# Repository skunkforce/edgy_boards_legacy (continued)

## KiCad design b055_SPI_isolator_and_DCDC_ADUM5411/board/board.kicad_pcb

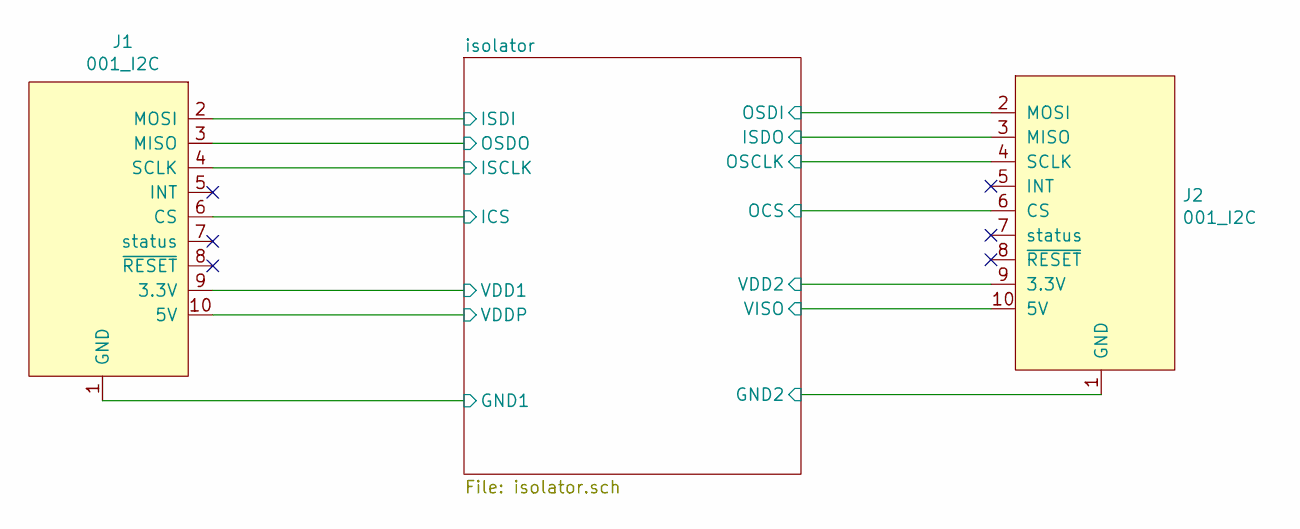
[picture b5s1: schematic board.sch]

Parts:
J1: 001_I2C; on_edge_2x05_device
J2: 001_I2C; on_edge_2x05_host

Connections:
/isolator/GND1: J1.1 (GND); also elsewhere on the board
/isolator/GND2: J2.1 (GND); also elsewhere on the board
/isolator/ICS: J1.6 (CS); also elsewhere on the board
/isolator/ISCLK: J1.4 (SCLK); also elsewhere on the board
/isolator/ISDI: J1.2 (MOSI); also elsewhere on the board
/isolator/ISDO: J2.3 (MISO); also elsewhere on the board
/isolator/OCS: J2.6 (CS); also elsewhere on the board
/isolator/OSCLK: J2.4 (SCLK); also elsewhere on the board
/isolator/OSDI: J2.2 (MOSI); also elsewhere on the board
/isolator/OSDO: J1.3 (MISO); also elsewhere on the board
/isolator/VDD1: J1.9 (3.3V); also elsewhere on the board
/isolator/VDD2: J2.9 (3.3V); also elsewhere on the board
/isolator/VDDP: J1.10 (5V); also elsewhere on the board
/isolator/VISO: J2.10 (5V); also elsewhere on the board

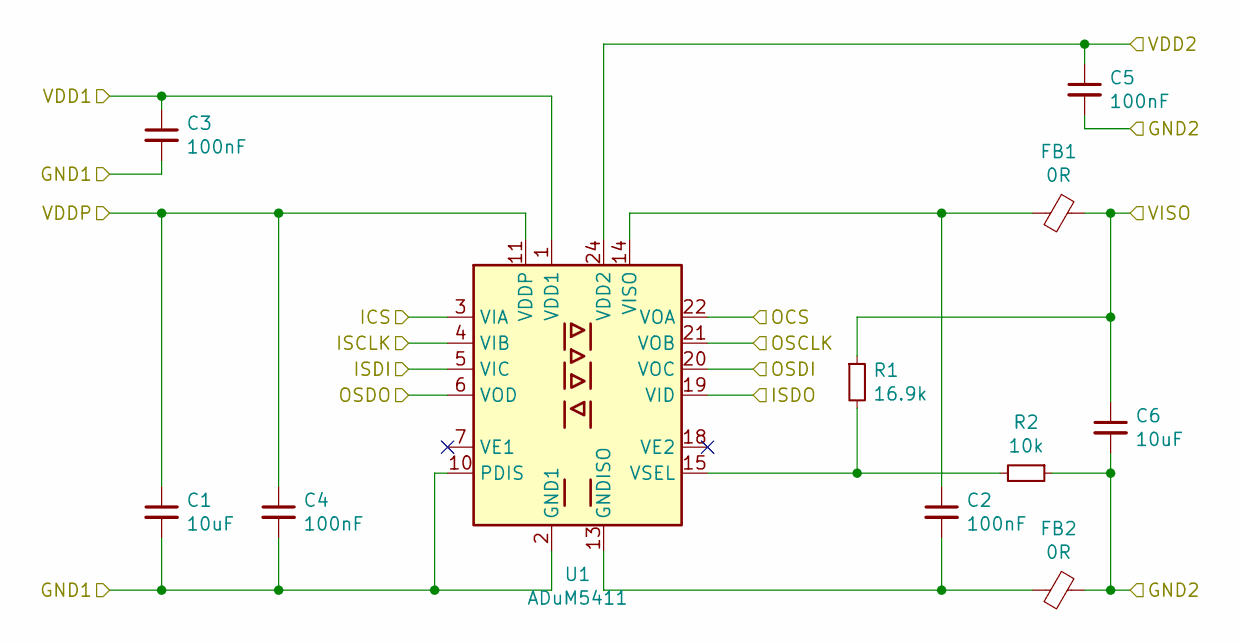
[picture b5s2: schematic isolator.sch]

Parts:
C1, C6: 10uF; C_0603_1608Metric
C2, C3, C4, C5: 100nF; C_0603_1608Metric
FB1, FB2: 0R; L_0805_2012Metric
R1: 16.9k; R_0603_1608Metric
R2: 10k; R_0603_1608Metric
U1: ADuM5411; SSOP-24_5.3x8.2mm_P0.65mm

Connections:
/isolator/GND1: C1.2, C3.2, C4.2, U1.2 (GND1), U1.9 (GND1), U1.10 (PDIS), U1.12 (GND1); also elsewhere on the board
/isolator/GND2: C5.2, C6.2, FB2.1, R2.1; also elsewhere on the board
/isolator/ICS: U1.3 (VIA); also elsewhere on the board
/isolator/ISCLK: U1.4 (VIB); also elsewhere on the board
/isolator/ISDI: U1.5 (VIC); also elsewhere on the board
/isolator/ISDO: U1.19 (VID); also elsewhere on the board
/isolator/OCS: U1.22 (VOA); also elsewhere on the board
/isolator/OSCLK: U1.21 (VOB); also elsewhere on the board
/isolator/OSDI: U1.20 (VOC); also elsewhere on the board
/isolator/OSDO: U1.6 (VOD); also elsewhere on the board
/isolator/VDD1: C3.1, U1.1 (VDD1); also elsewhere on the board
/isolator/VDD2: C5.1, U1.24 (VDD2); also elsewhere on the board
/isolator/VDDP: C1.1, C4.1, U1.11 (VDDP); also elsewhere on the board
/isolator/VISO: C6.1, FB1.1, R1.1; also elsewhere on the board
unnamed: C2.1, FB1.2, U1.14 (VISO)
unnamed: C2.2, FB2.2, U1.13 (GNDISO), U1.16 (GNDISO), U1.23 (GNDISO)
unnamed: R1.2, R2.2, U1.15 (VSEL)

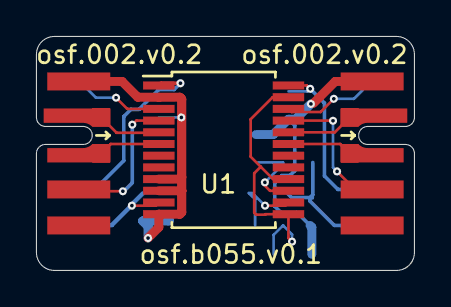
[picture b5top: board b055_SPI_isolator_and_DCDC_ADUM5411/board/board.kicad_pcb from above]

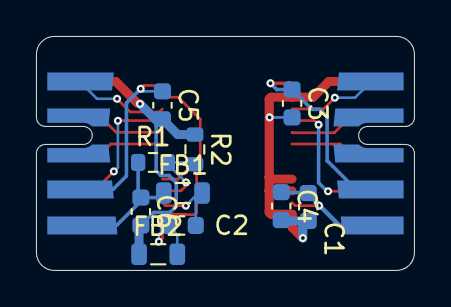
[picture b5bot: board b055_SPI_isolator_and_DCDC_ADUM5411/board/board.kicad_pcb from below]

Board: 2 copper layers, 21.0 x 13.0 mm, 13 parts (10 on the bottom side), 17 nets.

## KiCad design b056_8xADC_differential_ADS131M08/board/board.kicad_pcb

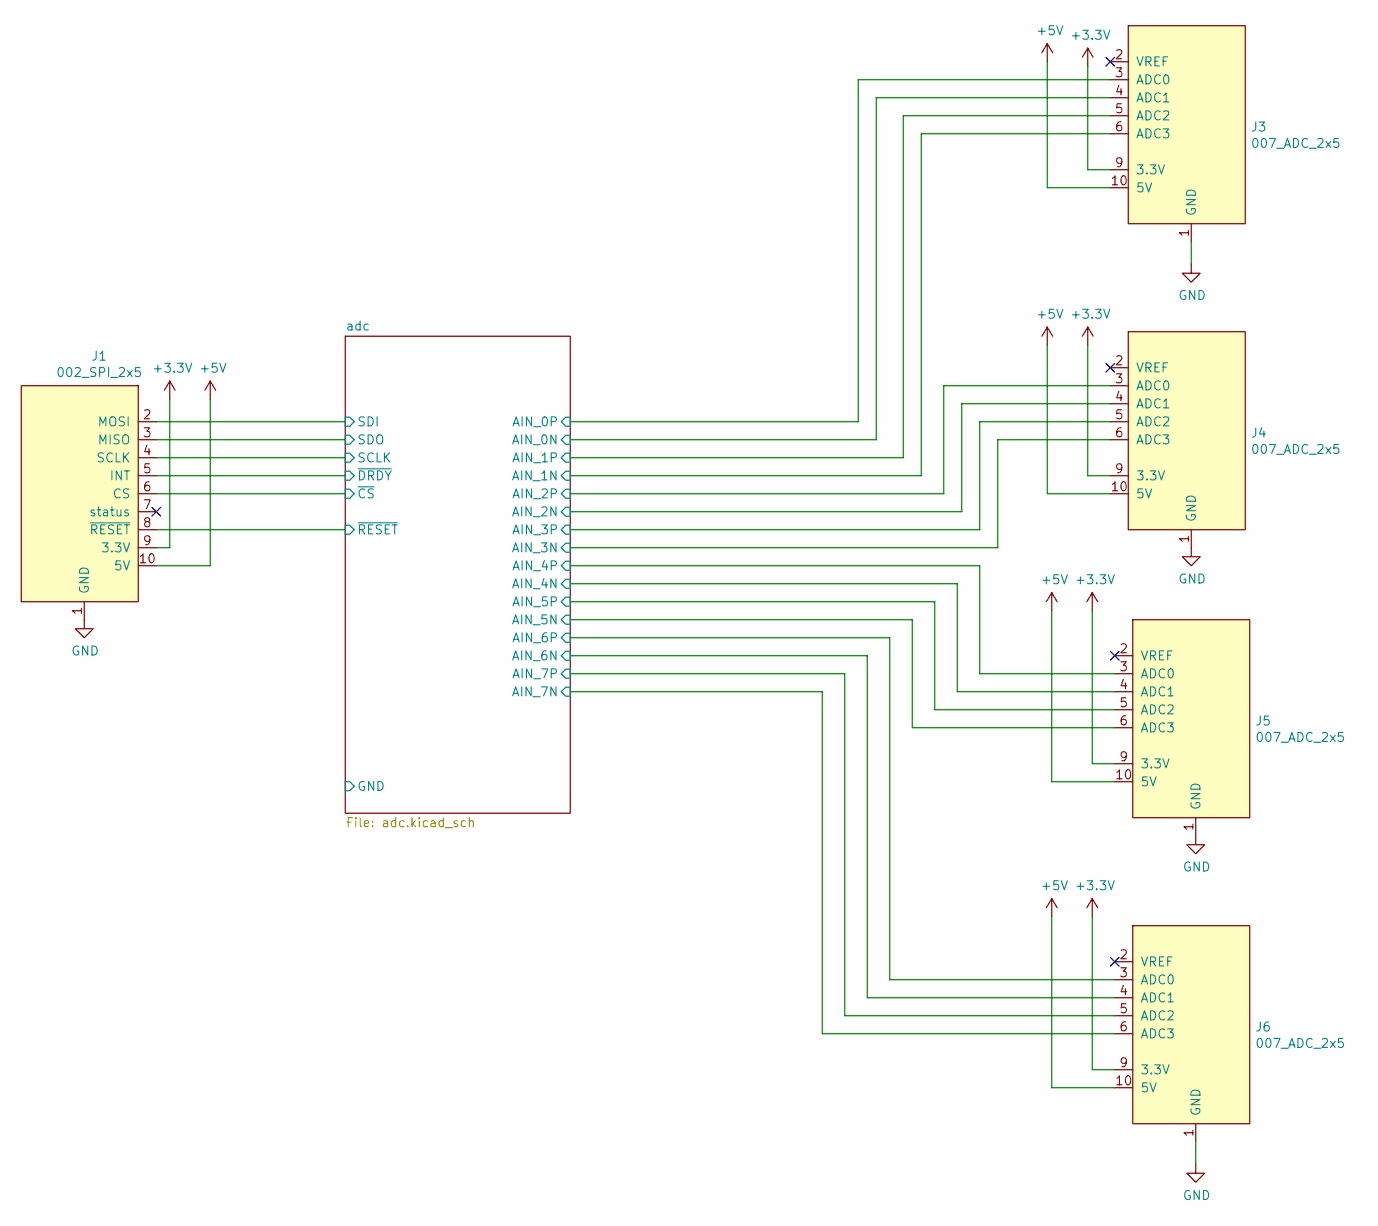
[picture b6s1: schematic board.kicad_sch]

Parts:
J1: 002_SPI_2x5; on_edge_2x05_device
J3, J4, J5, J6: 007_ADC_2x5; on_edge_2x05_host

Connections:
+3V3: J1.9 (3.3V), J3.9 (3.3V), J4.9 (3.3V), J5.9 (3.3V), J6.9 (3.3V); also elsewhere on the board
+5V: J1.10 (5V), J3.10 (5V), J4.10 (5V), J5.10 (5V), J6.10 (5V); also elsewhere on the board
/adc/AIN_0N: J3.4 (ADC1); also elsewhere on the board
/adc/AIN_0P: J3.3 (ADC0); also elsewhere on the board
/adc/AIN_1N: J3.6 (ADC3); also elsewhere on the board
/adc/AIN_1P: J3.5 (ADC2); also elsewhere on the board
/adc/AIN_2N: J4.4 (ADC1); also elsewhere on the board
/adc/AIN_2P: J4.3 (ADC0); also elsewhere on the board
/adc/AIN_3N: J4.6 (ADC3); also elsewhere on the board
/adc/AIN_3P: J4.5 (ADC2); also elsewhere on the board
/adc/AIN_4N: J5.4 (ADC1); also elsewhere on the board
/adc/AIN_4P: J5.3 (ADC0); also elsewhere on the board
/adc/AIN_5N: J5.6 (ADC3); also elsewhere on the board
/adc/AIN_5P: J5.5 (ADC2); also elsewhere on the board
/adc/AIN_6N: J6.4 (ADC1); also elsewhere on the board
/adc/AIN_6P: J6.3 (ADC0); also elsewhere on the board
/adc/AIN_7N: J6.6 (ADC3); also elsewhere on the board
/adc/AIN_7P: J6.5 (ADC2); also elsewhere on the board
/adc/SCLK: J1.4 (SCLK); also elsewhere on the board
/adc/SDI: J1.2 (MOSI); also elsewhere on the board
/adc/SDO: J1.3 (MISO); also elsewhere on the board
/adc/~CS: J1.6 (CS); also elsewhere on the board
/adc/~DRDY: J1.5 (INT); also elsewhere on the board
/adc/~RESET: J1.8 (~RESET); also elsewhere on the board
GND: J1.1 (GND), J3.1 (GND), J4.1 (GND), J5.1 (GND), J6.1 (GND); also elsewhere on the board

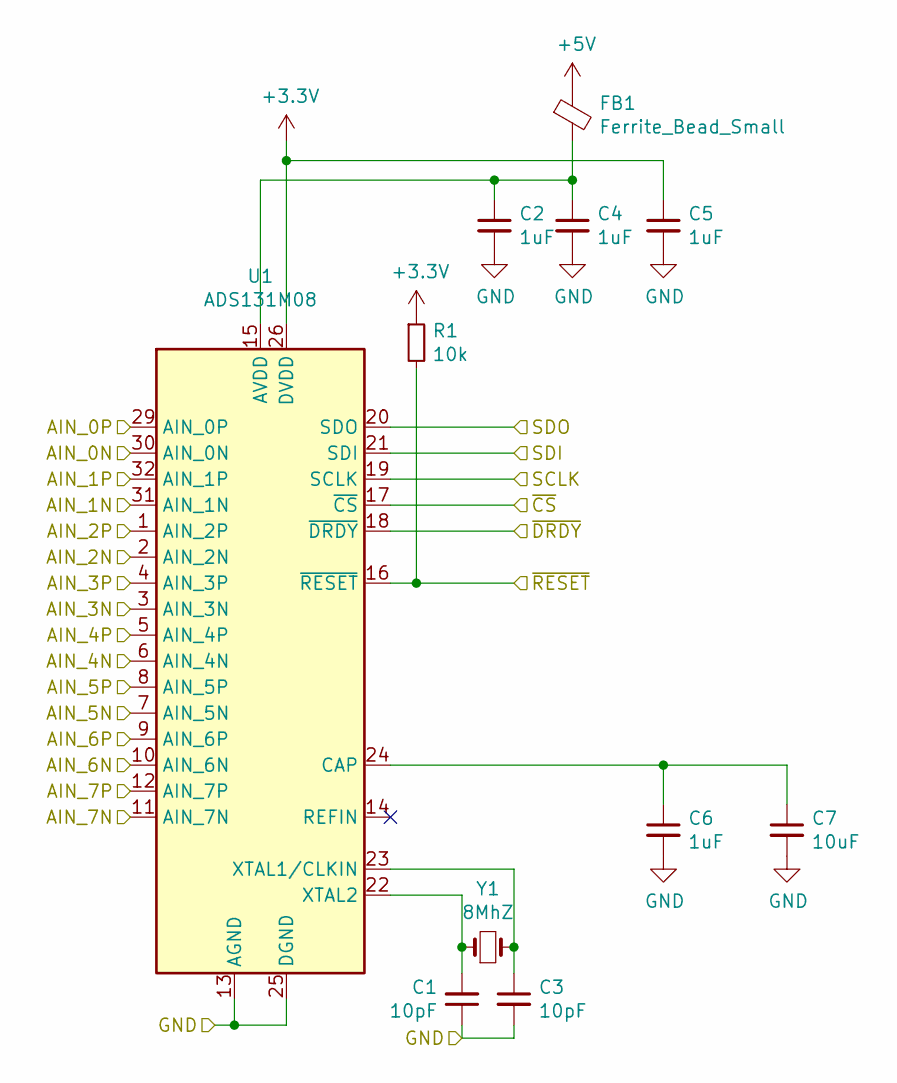
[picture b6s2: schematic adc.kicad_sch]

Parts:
C1, C3: 10pF; C_0603_1608Metric
C2, C4, C5, C6: 1uF; C_0603_1608Metric
C7: 10uF; C_0603_1608Metric
FB1: Ferrite_Bead_Small; L_0603_1608Metric
R1: 10k; R_0603_1608Metric
U1: ADS131M08; QFN-32-1EP_4x4mm_P0.4mm_EP2.9x2.9mm
Y1: 8MhZ; Crystal_SMD_5032-2Pin_5.0x3.2mm

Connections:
+3V3: C5.1, R1.1, U1.26 (DVDD); also elsewhere on the board
+5V: FB1.1; also elsewhere on the board
/adc/AIN_0N: U1.30 (AIN_0N); also elsewhere on the board
/adc/AIN_0P: U1.29 (AIN_0P); also elsewhere on the board
/adc/AIN_1N: U1.31 (AIN_1N); also elsewhere on the board
/adc/AIN_1P: U1.32 (AIN_1P); also elsewhere on the board
/adc/AIN_2N: U1.2 (AIN_2N); also elsewhere on the board
/adc/AIN_2P: U1.1 (AIN_2P); also elsewhere on the board
/adc/AIN_3N: U1.3 (AIN_3N); also elsewhere on the board
/adc/AIN_3P: U1.4 (AIN_3P); also elsewhere on the board
/adc/AIN_4N: U1.6 (AIN_4N); also elsewhere on the board
/adc/AIN_4P: U1.5 (AIN_4P); also elsewhere on the board
/adc/AIN_5N: U1.7 (AIN_5N); also elsewhere on the board
/adc/AIN_5P: U1.8 (AIN_5P); also elsewhere on the board
/adc/AIN_6N: U1.10 (AIN_6N); also elsewhere on the board
/adc/AIN_6P: U1.9 (AIN_6P); also elsewhere on the board
/adc/AIN_7N: U1.11 (AIN_7N); also elsewhere on the board
/adc/AIN_7P: U1.12 (AIN_7P); also elsewhere on the board
/adc/SCLK: U1.19 (SCLK); also elsewhere on the board
/adc/SDI: U1.21 (SDI); also elsewhere on the board
/adc/SDO: U1.20 (SDO); also elsewhere on the board
/adc/~CS: U1.17 (~CS); also elsewhere on the board
/adc/~DRDY: U1.18 (~DRDY); also elsewhere on the board
/adc/~RESET: R1.2, U1.16 (~RESET); also elsewhere on the board
GND: C1.1, C2.2, C3.2, C4.2, C5.2, C6.2, C7.2, U1.13 (AGND), U1.25 (DGND), U1.28 (AGND), U1.33 (AGND); also elsewhere on the board
unnamed: C1.2, U1.22 (XTAL2), Y1.1
unnamed: C2.1, C4.1, FB1.2, U1.15 (AVDD)
unnamed: C3.1, U1.23 (XTAL1/CLKIN), Y1.2
unnamed: C6.1, C7.1, U1.24 (CAP)

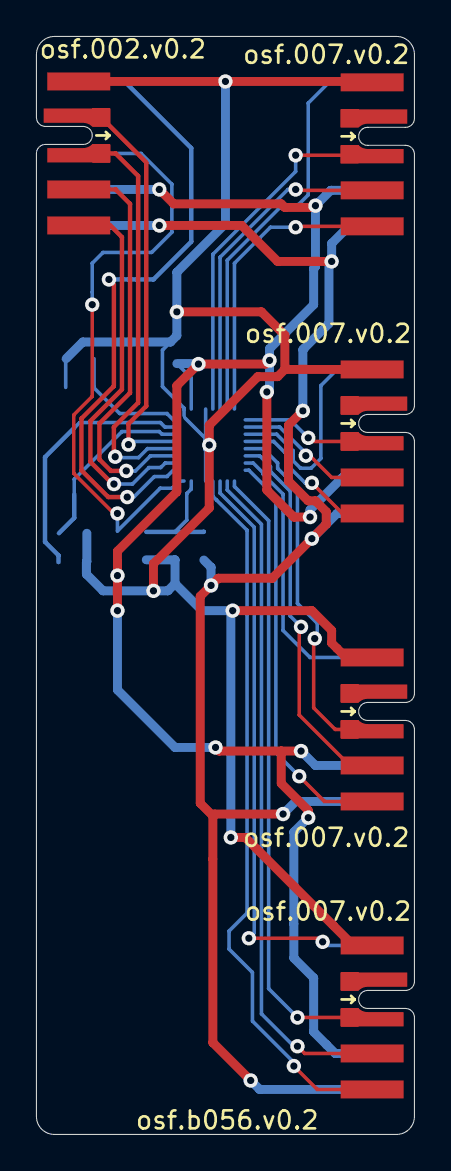
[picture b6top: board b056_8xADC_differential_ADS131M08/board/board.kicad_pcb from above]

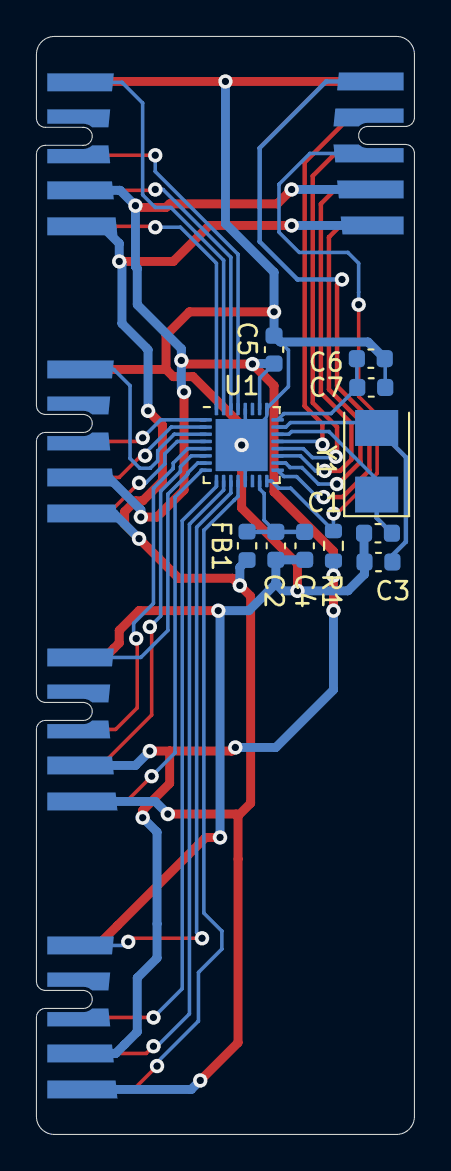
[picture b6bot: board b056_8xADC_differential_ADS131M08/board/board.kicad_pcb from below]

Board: 2 copper layers, 21.0 x 61.0 mm, 16 parts (11 on the bottom side), 29 nets.

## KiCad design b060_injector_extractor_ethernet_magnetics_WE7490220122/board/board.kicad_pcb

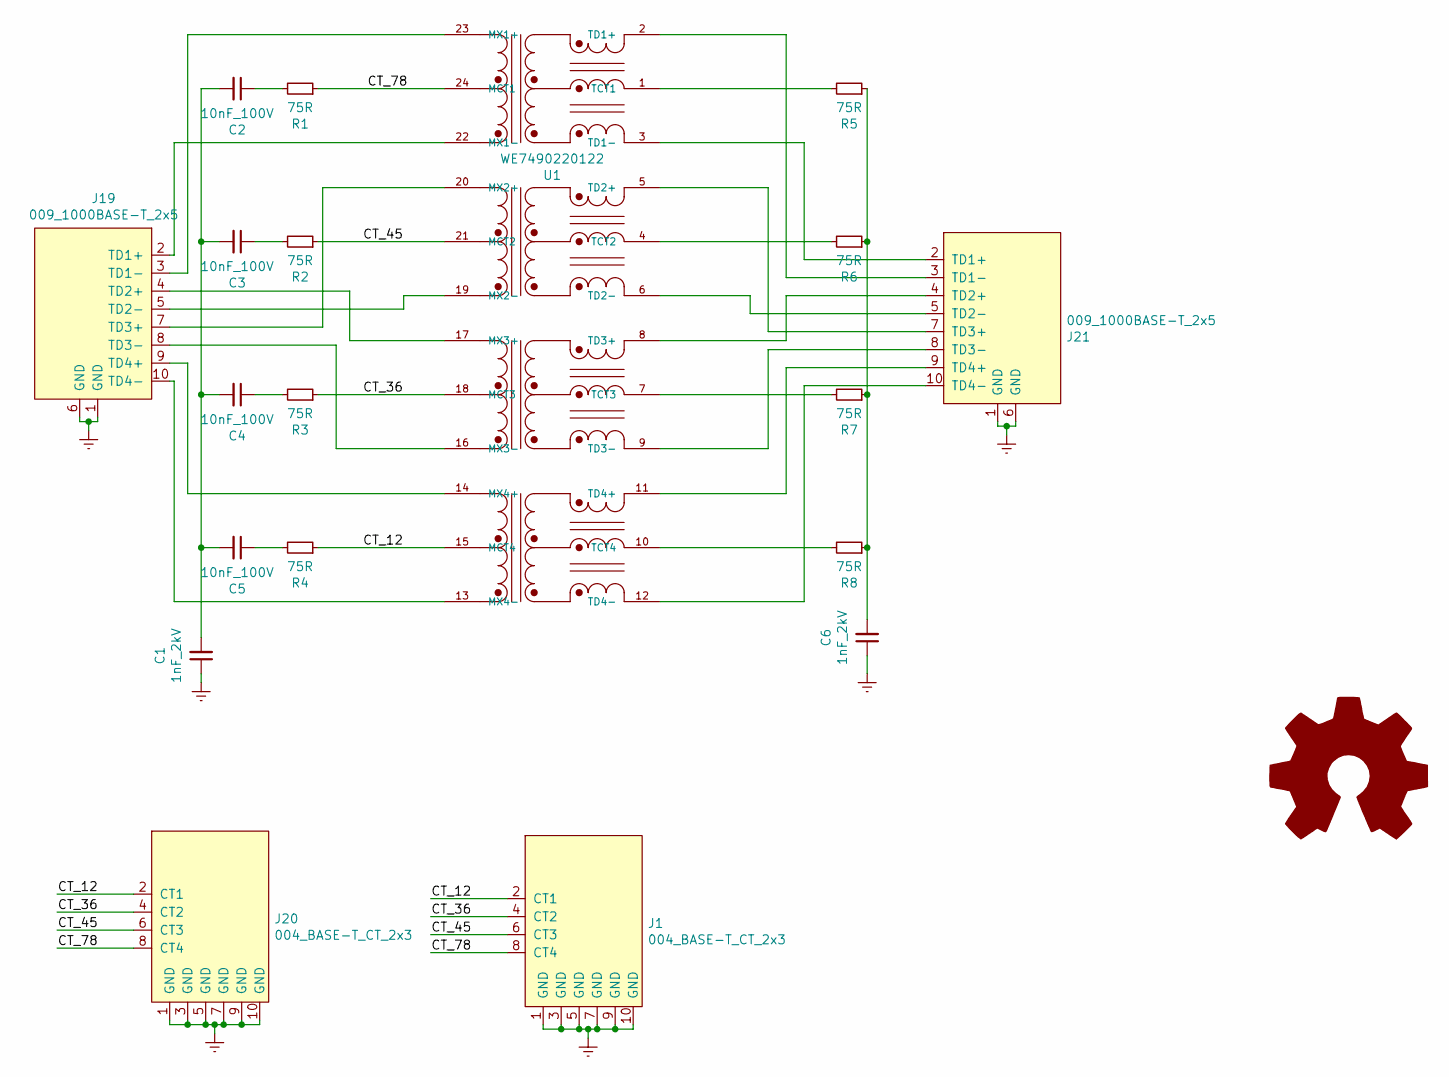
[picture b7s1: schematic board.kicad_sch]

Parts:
C1, C6: 1nF_2kV; C_1210_3225Metric; Voltage 2000; MPN CL32B102KJFNNNE
C2, C3, C4, C5: 10nF_100V; C_0603_1608Metric; Voltage 100; MPN ‎CL10B103KC8NNNC‎
J1: 004_BASE-T_CT_2x3; on_edge_2x05_device
J19, J21: 009_1000BASE-T_2x5; on_edge_2x05_host
J20: 004_BASE-T_CT_2x3; on_edge_2x05_host
R1, R2, R3, R4, R5, R6, R7, R8: 75R; R_0805_2012Metric; MPN ‎RMCF0805FT75R0‎
U1: WE7490220122; XFMR_7490220122; MPN 7490220122; Digi-Key_PN 732-10731-1-ND
l1: Logo_Open_Hardware_Large; OSHW-Logo2_7.3x6mm_SilkScreen

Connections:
/CT_12: J1.2 (CT1), J20.2 (CT1), R4.1, U1.15 (MCT4)
/CT_36: J1.4 (CT2), J20.4 (CT2), R3.1, U1.18 (MCT3)
/CT_45: J1.6 (CT3), J20.6 (CT3), R2.1, U1.21 (MCT2)
/CT_78: J1.8 (CT4), J20.8 (CT4), R1.1, U1.24 (MCT1)
Earth: C1.1, C6.1, J1.1 (GND), J1.3 (GND), J1.5 (GND), J1.7 (GND), J1.9 (GND), J1.10 (GND), J19.1 (GND), J19.6 (GND), J20.1 (GND), J20.3 (GND), J20.5 (GND), J20.7 (GND), J20.9 (GND), J20.10 (GND), J21.1 (GND), J21.6 (GND)
unnamed: C1.2, C2.2, C3.2, C4.2, C5.2
unnamed: C2.1, R1.2
unnamed: C3.1, R2.2
unnamed: C4.1, R3.2
unnamed: C5.1, R4.2
unnamed: C6.2, R5.1, R6.1, R7.1, R8.1
unnamed: J19.2 (TD1+), U1.22 (MX1-)
unnamed: J19.3 (TD1-), U1.23 (MX1+)
unnamed: J19.4 (TD2+), U1.17 (MX3+)
unnamed: J19.5 (TD2-), U1.19 (MX2-)
unnamed: J19.7 (TD3+), U1.20 (MX2+)
unnamed: J19.8 (TD3-), U1.16 (MX3-)
unnamed: J19.9 (TD4+), U1.14 (MX4+)
unnamed: J19.10 (TD4-), U1.13 (MX4-)
unnamed: J21.2 (TD1+), U1.3 (TD1-)
unnamed: J21.3 (TD1-), U1.2 (TD1+)
unnamed: J21.4 (TD2+), U1.8 (TD3+)
unnamed: J21.5 (TD2-), U1.6 (TD2-)
unnamed: J21.7 (TD3+), U1.5 (TD2+)
unnamed: J21.8 (TD3-), U1.9 (TD3-)
unnamed: J21.9 (TD4+), U1.11 (TD4+)
unnamed: J21.10 (TD4-), U1.12 (TD4-)
unnamed: R5.2, U1.1 (TCT1)
unnamed: R6.2, U1.4 (TCT2)
unnamed: R7.2, U1.7 (TCT3)
unnamed: R8.2, U1.10 (TCT4)

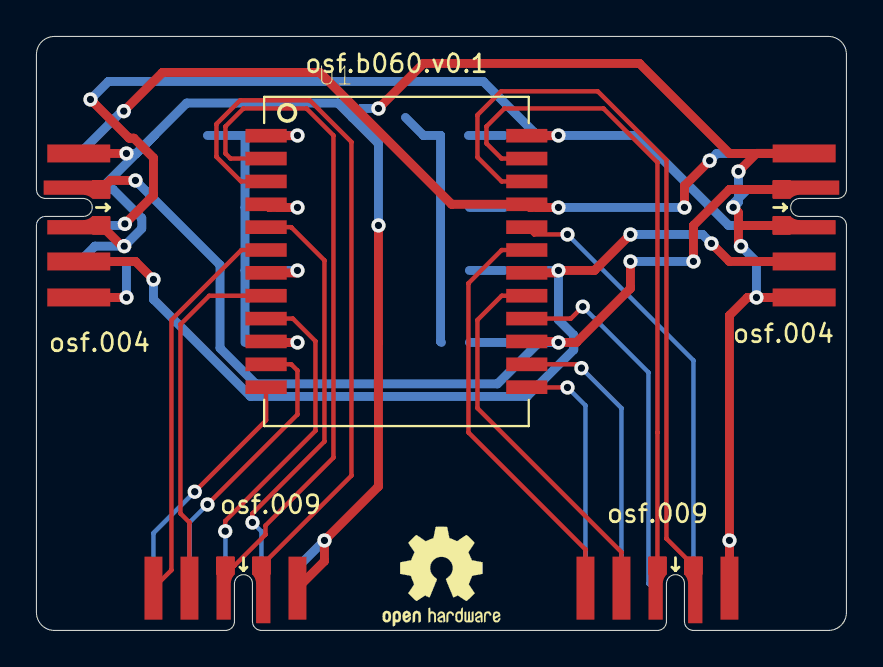
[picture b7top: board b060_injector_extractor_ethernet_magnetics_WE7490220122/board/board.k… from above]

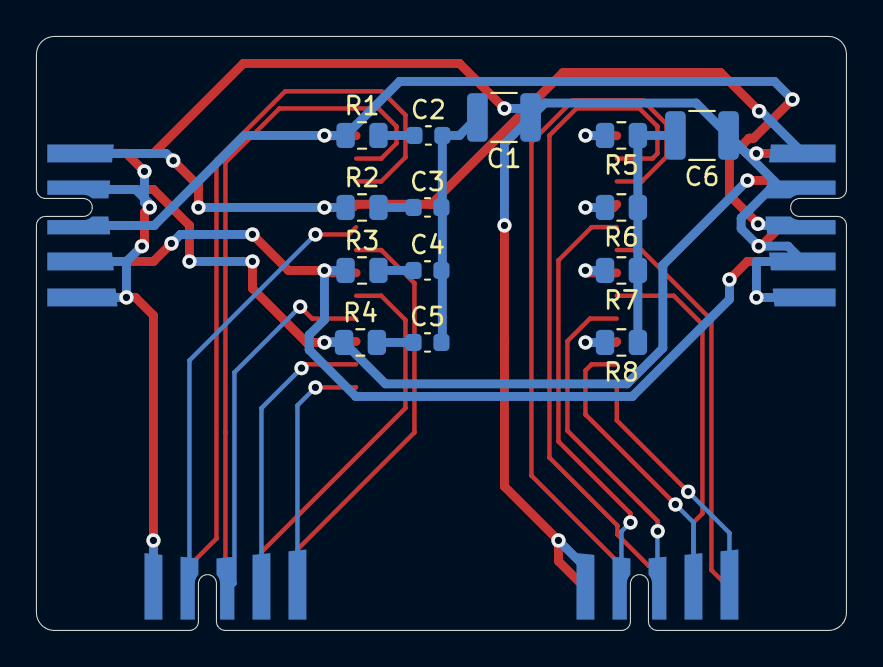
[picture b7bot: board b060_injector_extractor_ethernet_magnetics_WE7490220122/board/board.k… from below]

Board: 2 copper layers, 45.0 x 33.0 mm, 20 parts (14 on the bottom side), 31 nets.
